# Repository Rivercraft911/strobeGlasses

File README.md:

# Strobe Glasses

Have you been seeing too much? Disappointed by the lack of stuttering in your reality? Introducing Strobe Glasses.

Open-source strobe glasses for experimenting with visual reaction-time training.

One LCD light valve slides into each side of the frame and switches between
light and dark at an adjustable rate. The goal is a small, USB-C rechargeable
control board that fits into a resin-printed glasses frame.

The MK1 PCB uses an ATtiny402, with USB-C charging and an output for each eye.

[KiCad project](strobeGlassesMK1/) · [Electronic parts](hardware-library/BOM.md) · [Glasses STEP](mechanical/strobe-glasses-mk1.step) · [Print and assemble](mechanical/TOP_LOAD.md) · [Firmware](firmware/strobe_glasses/)

Electrical decay after disabling the 5 V PSU output (90–10%: 477 ms).
Shorting the valve leads clears it much faster.

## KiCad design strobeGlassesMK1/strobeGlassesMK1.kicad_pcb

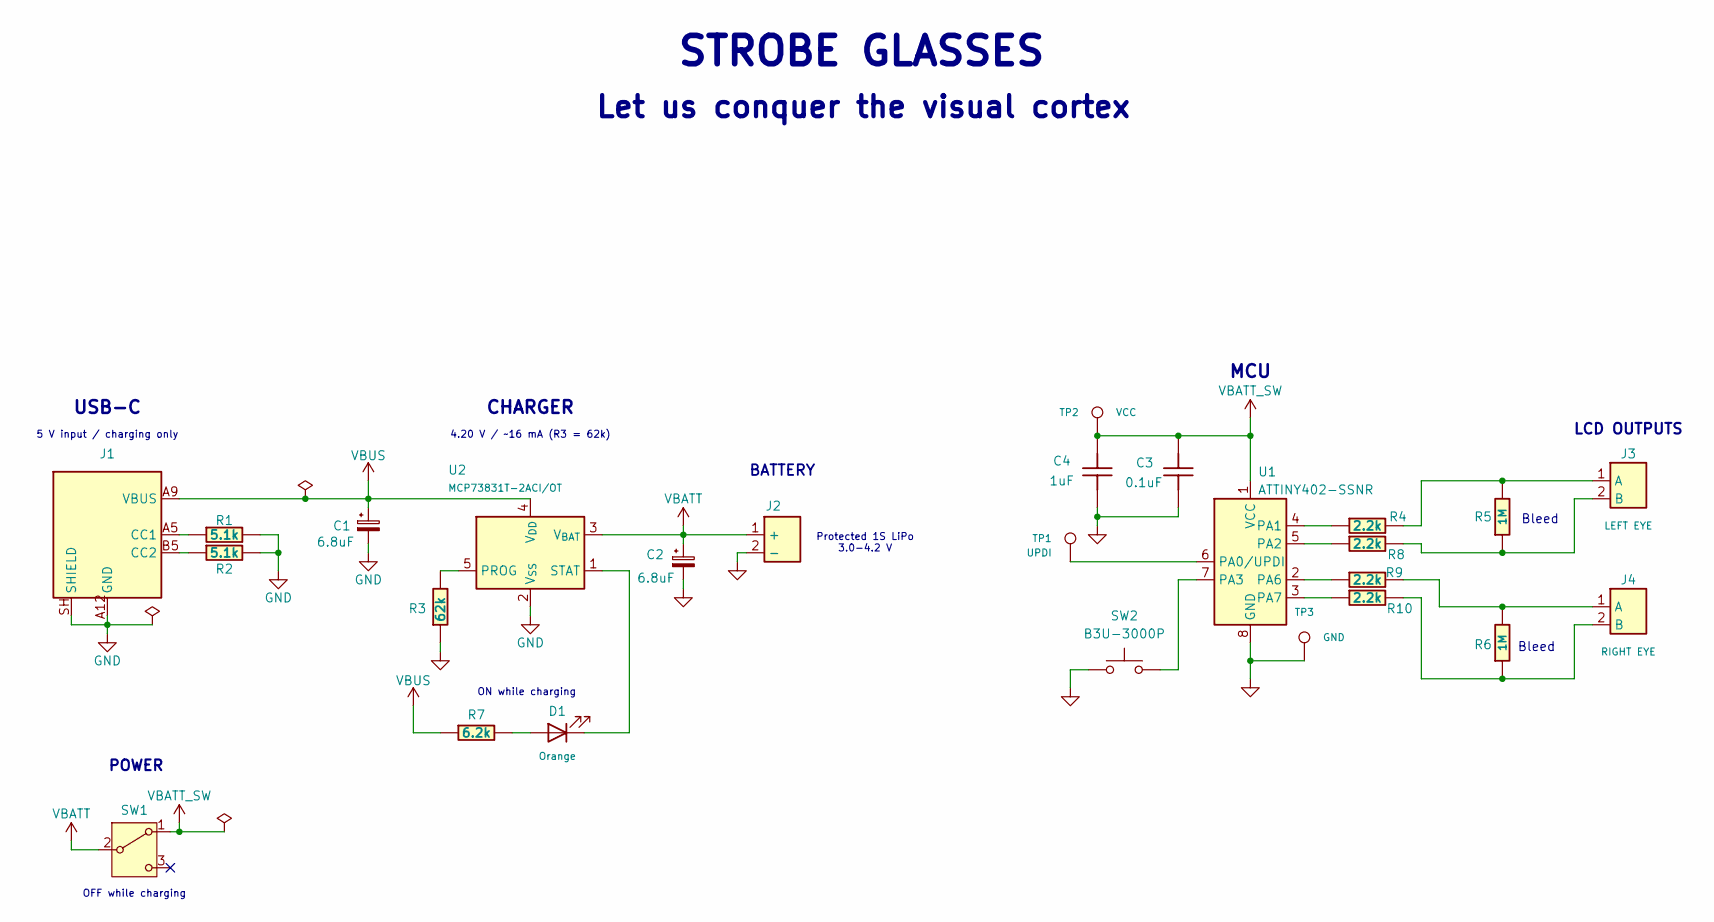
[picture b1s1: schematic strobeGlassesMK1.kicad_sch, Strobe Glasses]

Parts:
C1, C2: 6.8uF; T491A685K016AT; Rating 6.8 µF, 16 V, ±10%, polarized tantalum; MPN T491A685K016AT; DigiKey Part Number 399-10132-1-ND
C3: 0.1uF; C1608X7R1H104K080AA; Rating 100 nF, 50 V, X7R, ±10%, 0603; MPN C1608X7R1H104K080AA; DigiKey Part Number 445-1314-1-ND
C4: 1uF; CL10A105KP8NNNC; Rating 1 µF, 10 V, X5R, ±10%, 0603; MPN CL10A105KP8NNNC; DigiKey Part Number 1276-1182-1-ND
D1: Orange; LTST-C190KFKT; Rating Orange charge LED, 0603; MPN LTST-C190KFKT; DigiKey Part Number 160-1434-1-ND
J1: USB4125-GF-A; MPN USB4125-GF-A; DigiKey Part Number 2073-USB4125-GF-ACT-ND
J2: JST-SH 1mm; SM02B-SRSS-TB; MPN SM02B-SRSS-TB; DigiKey Part Number 455-SM02B-SRSS-TBCT-ND
J3: LEFT EYE; SM02B-SRSS-TB_LCD; MPN SM02B-SRSS-TB; DigiKey Part Number 455-SM02B-SRSS-TBCT-ND
J4: RIGHT EYE; SM02B-SRSS-TB_LCD; MPN SM02B-SRSS-TB; DigiKey Part Number 455-SM02B-SRSS-TBCT-ND
R1, R2: 5.1k; CRCW06035K10FKEA; Rating 5.1kohm ±1%, 0.125W, 0603; MPN CRCW06035K10FKEA; DigiKey Part Number 541-5.10KHCT-ND
R3: 62k; RC0603FR-0762KL; Rating 62.0 kΩ, ±1%, 0.1 W, 0603; MPN RC0603FR-0762KL; DigiKey Part Number 311-62.0KHRCT-ND
R4, R8, R9, R10: 2.2k; RC0603FR-072K2L; Rating 2.2 kΩ, ±1%, 0.1 W, 0603; MPN RC0603FR-072K2L; DigiKey Part Number 311-2.20KHRCT-ND
R5, R6: 1M; RC0603FR-071ML; Rating 1 MΩ, ±1%, 0.1 W, 0603; MPN RC0603FR-071ML; DigiKey Part Number 311-1.00MHRCT-ND
R7: 6.2k; RC0603FR-076K2L; Rating 6.2 kΩ, ±1%, 0.1 W, 0603; MPN RC0603FR-076K2L; DigiKey Part Number 311-6.20KHRCT-ND
SW1: SLW-662712-15A-SMT-TR; Rating SPDT, non-shorting, 6VDC, 300mA; body6.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; MPN SLW-662712-15A-SMT-TR; DigiKey Part Number 2223-SLW-662712-15A-SMT-TRCT-ND
SW2: B3U-3000P; Rating Side-actuated preset button; MPN B3U-3000P; DigiKey Part Number SW1022CT-ND
TP1: UPDI; TestPoint_Pad_D1.0mm
TP2: VCC; TestPoint_Pad_D1.0mm
TP3: GND; TestPoint_Pad_D1.0mm
U1: ATTINY402-SSNR; Rating 4 KB MCU, SOIC-8; MPN ATTINY402-SSNR; DigiKey Part Number ATTINY402-SSNRCT-ND
U2: MCP73831T-2ACI/OT; MCP73831T-2ACI_OT; Rating 4.20 V single-cell LiPo charger; MPN MCP73831T-2ACI/OT; DigiKey Part Number MCP73831T-2ACI/OTCT-ND

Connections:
GND: C1.2, C2.2, C3.2, C4.2, J1.A12 (GND), J1.B12 (GND), J1.SH (SHIELD), J2.2 (−), R1.2, R2.2, R3.1, SW2.1, TP3.1 (1_1), U1.8 (GND), U2.2 (V_{SS})
unnamed: D1.2 (A), R7.2
unnamed: D1.1 (K), U2.1 (STAT)
unnamed: J1.A5 (CC1), R1.1
unnamed: J1.B5 (CC2), R2.1
unnamed: J3.1 (A), R4.2, R5.2
unnamed: J3.2 (B), R5.1, R8.2
unnamed: J4.1 (A), R6.2, R9.2
unnamed: J4.2 (B), R6.1, R10.2
unnamed: TP1.1 (1_1), U1.6 (PA0/UPDI)
unnamed: R4.1, U1.4 (PA1)
unnamed: R8.1, U1.5 (PA2)
unnamed: SW2.2, U1.7 (PA3)
unnamed: R9.1, U1.2 (PA6)
unnamed: R10.1, U1.3 (PA7)
unnamed: R3.2, U2.5 (PROG)
VBATT: C2.1, J2.1 (+), SW1.2 (B), U2.3 (V_{BAT})
VBATT_SW: C3.1, C4.1, SW1.1 (A), TP2.1 (1_1), U1.1 (VCC)
VBUS: C1.1, J1.A9 (VBUS), J1.B9 (VBUS), R7.1, U2.4 (V_{DD})

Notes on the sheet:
Bleed
BATTERY
ON while charging
Protected 1S LiPo 3.0-4.2 V
USB-C
CHARGER
POWER
4.20 V / ~16 mA (R3 = 62k)
MCU
OFF while charging
LCD OUTPUTS
Let us conquer the visual cortex
STROBE GLASSES
5 V input / charging only

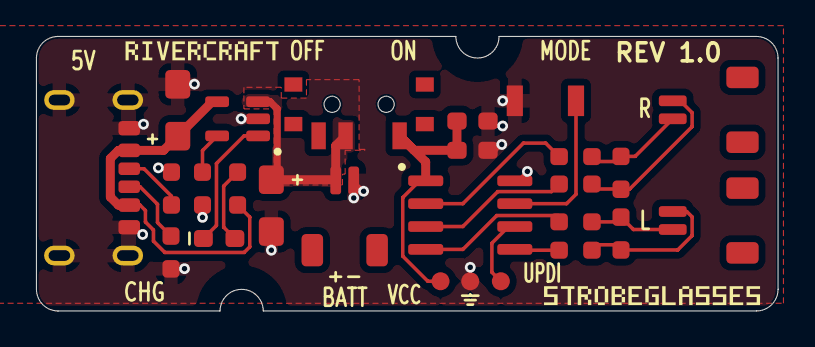
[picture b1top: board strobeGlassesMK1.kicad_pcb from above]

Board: 2 copper layers, 41.2 x 15.2 mm, 26 parts (0 on the bottom side), 19 nets.

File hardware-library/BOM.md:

# Order BOM

For **one fully populated PCB**: 23 purchased components, 15 order lines. TP1/TP2/TP3 are copper test pads and require no purchased parts. D1/R7 are included for the charge indicator.

- [DigiKey import: exact one-board quantities](digikey-bom.csv)
- [DigiKey import: one board with hand-assembly spares](digikey-bom-with-spares.csv)
- [DigiKey import: SH wiring parts](digikey-wiring.csv)
- [Independent board review](BOARD_REVIEW.md)

Use DigiKey “Upload a List” and map the part-number, quantity and reference columns. Select cut tape, not Digi-Reel. The spare list orders two each of ICs/switches/USB, five SH headers, four tantalum capacitors, ten of each small passive and five LEDs. Batteries, lenses and programmer are separate below.

| Qty | Refs | Part / value | Order MPN (DigiKey link) | DigiKey number |
| ---: | --- | --- | --- | --- |
| 1 | U1 | ATtiny402 MCU; SOIC-8 | [ATTINY402-SSNR](https://www.digikey.com/en/products/detail/microchip-technol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 | ATTINY402-SSNRCT-ND |
| 1 | U2 | 4.20 V LiPo charger; SOT-23-5 | [MCP73831T-2ACI/OT](https://www.digikey.com/en/products/detail/microchip-technol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 | MCP73831T-2ACI/OTCT-ND |
| 1 | J1 | 6-contact power-only USB-C; exact blank-suffix variant | [USB4125-GF-A](https://www.digikey.com/en/products/detail/gct/USB4125-GF-A/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 | 2073-USB4125-GF-ACT-ND |
| 3 | J2, J3, J4 | 2-pin JST-SH 1 mm right-angle headers | [SM02B-SRSS-TB](https://www.digikey.com/en/products/detail/jst-sales-america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 | 455-SM02B-SRSS-TBCT-ND |
| 1 | SW1 | Hard power slide switch | [SLW-662712-15A-SMT-TR](https://www.digikey.com/en/products/detail/same-sky-formerly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 | 2223-SLW-662712-15A-SMT-TRCT-ND |
| 1 | SW2 | Side-actuated preset button | [B3U-3000P](https://www.digikey.com/en/products/detail/omron-electronics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 | SW1022CT-ND |
| 2 | C1, C2 | 6.8 uF 16 V tantalum; KEMET A-case; polarized | [T491A685K016AT](https://www.digikey.com/en/products/detail/kemet/T491A685K01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 | 399-10132-1-ND |
| 1 | C3 | 100 nF 50 V X7R; 0603 | [C1608X7R1H104K080AA](https://www.digikey.com/en/products/detail/tdk/C1608X7R1H104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 | 445-1314-1-ND |
| 1 | C4 | 1 uF 10 V X5R; 0603 | [CL10A105KP8NNNC](https://www.digikey.com/en/products/detail/samsung-electro-m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 | 1276-1182-1-ND |
| 2 | R1, R2 | 5.1 kohm 1% 0.125 W; 0603; USB CC pull-downs | [CRCW06035K10FKEA](https://www.digikey.com/en/products/detail/vishay-dale/CRCW0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 | 541-5.10KHCT-ND |
| 1 | R3 | 62 kohm 1% 0.1 W; 0603; ~16.1 mA charge setting | [RC0603FR-0762KL](https://www.digikey.com/en/products/detail/yageo/RC0603FR-07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 | 311-62.0KHRCT-ND |
| 4 | R4, R8, R9, R10 | 2.2 kohm 1% 0.1 W; 0603; four LCD series resistors | [RC0603FR-072K2L](https://www.digikey.com/en/products/detail/yageo/RC0603FR-07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 | 311-2.20KHRCT-ND |
| 2 | R5, R6 | 1 Mohm 1% 0.1 W; 0603; eye bleeders | [RC0603FR-071ML](https://www.digikey.com/en/products/detail/yageo/RC0603FR-07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 | 311-1.00MHRCT-ND |
| 1 | R7 | 6.2 kohm 1% 0.125 W; 0603; charge LED resistor | [CRCW06036K20FKEA](https://www.digikey.com/en/products/detail/vishay-dale/CRCW0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 | 541-6.20KHCT-ND |
| 1 | D1 | Orange LED; 0603; pad 1 cathode | [LTST-C190KFKT](https://www.digikey.com/en/products/detail/liteon/LTST-C190K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 | 160-1434-1-ND |

**R7 substitution:** the selected Yageo RC0603FR-076K2L showed zero stock. The order files use Vishay CRCW06036K20FKEA, an equivalent 6.2 kohm, 1%, 0603 part with a higher 0.125 W rating. CAD selection is unchanged. Omit both R7 and D1 if you do not want a charge indicator.

All order lines above showed stock during the 2026-11-08 US DigiKey check. The exact one-board PCB parts total is about **$7.41** at the displayed one-piece prices, before shipping/tax/tariffs. Quantity discounts may lower it. Stock and checkout prices can change.

## Wiring and offboard items

| Qty | Item | MPN / DigiKey link | DigiKey number | When needed |
| ---: | --- | --- | --- | --- |
| 3 | JST-SH 2-pin cable housings | [SHR-02V-S-B](https://www.digikey.com/en/products/detail/jst-sales-america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 | 455-1377-ND | One per cable; two for eyes, plus battery adapter if reusing the PH pack. One is spare if buying the factory-SH battery. |
| 6 | Black 28 AWG precrimped wires, 152.4 mm, socket at both ends | [ASSHSSH28K152](https://www.digikey.com/en/products/detail/jst-sales-america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 | 455-3076-ND | Lets you keep long leads for three pigtails. Cut near one end or split into shorter leads; three assemblies suffice if halved. Mark polarity clearly. |
| 1 optional | PH male pigtail for on-hand Adafruit battery | [Adafruit 3814](https://www.digikey.com/en/products/detail/adafruit-industri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 | 1528-2617-ND | Splice to an SH pigtail to adapt the existing PH battery without changing its factory lead. Not needed with the SparkFun 40 mAh pack. |
| 1 if needed | UPDI programmer, cable included | [Adafruit 5879](https://www.digikey.com/en/products/detail/adafruit-industri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 | 1528-5879-ND | If you do not already own a suitable UPDI programmer. Temporarily wire to TP1/TP2/TP3. |
| 4 total | Small LCD light valves | [Adafruit 3627](https://www.digikey.com/en/products/detail/adafruit-industri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 | 1528-2516-ND | Two stacked, electrically parallel per eye. Buy only any shortfall from the valves already on hand. |

## Battery choice

Use the protected Adafruit/PKCELL 105 mAh pack already on hand for first bring-up, or try **[SparkFun 25270, 40 mAh](https://www.digikey.com/en/products/detail/sparkfun-electron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 / **1568-25270-ND** for the smaller build. The latter showed 267 in stock at $7.39. The finished protected pack is at most 22 × 11.5 × 3.5 mm, and its datasheet specifies SHR-02V-S-B with pin 1 red(+)/pin 2 black(-), matching J2 directly.

The 40 mAh pack specifies 8 mA standard charge and 20 mA maximum. This board is ~16.1 mA nominal, so it is below the maximum, with margin in the checked datasheet corners. Its taper endpoint differs from the charger; measure usable capacity/current on the final board before promising runtime. Keep R3 = 62 kΩ: arbitrarily increasing RPROG past 67 kΩ is outside the MCP73831 specified range and approaches shutdown detection.

Battery size can shrink now without changing the PCB, because only its connector is modeled. Keep enclosure clearance for the entire protected pack, its lead and the connector. Confirm actual cable polarity before connection. Measure the final ATtiny board current before choosing the final capacity.

[40 mAh pack specification](https://cdn.sparkfun.com/assets/4/f/c/6/3/SPE-DTP301120SH-3.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 · [SparkFun product](https://www.sparkfun.com/polymer-lithium-ion-battery-40mah-j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

## First-board conditions

- Charge with SW1 OFF; the charger has no load sharing. Use a protected 1S LiPo (3.7 V nominal, 4.2 V full).
- Program a conservative 5 MHz or slower ATtiny application, with balanced positive/negative LCD drive, clear-on-reset, button pull-up/debounce and brownout/low-battery handling.
- For UPDI Friend bring-up: SW1 OFF, Friend at 3.3 V, PWR to TP2, GND to TP3 and UPDI to TP1. Avoid tying its power output to a battery-driven rail.
- Check actual charging current, UPDI operation, lens voltage/contrast and board battery current on the assembled prototype. Mechanical fit follows; no PCB change is currently required by the review.

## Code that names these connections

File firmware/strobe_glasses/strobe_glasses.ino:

#include <Arduino.h>
#include <avr/eeprom.h>
#include <avr/interrupt.h>
#include <avr/sleep.h>
#include <avr/wdt.h>
#include <util/atomic.h>

#if !defined(__AVR_ATtiny402__) || F_CPU != 5000000UL
#error "Select ATtiny402 and 5 MHz internal."
#endif
#if !defined(MILLIS_USE_TIMERA0) && !defined(MILLIS_USE_TIMERNONE)
#error "Use the default ATtiny402 millis timer (TCA0) or disable millis."
#endif

// MK1: PA0 stays dedicated to UPDI. The charge LED has no MCU connection.
constexpr uint8_t LensPins = PIN1_bm | PIN2_bm | PIN6_bm | PIN7_bm;
constexpr uint8_t ButtonPin = PIN3_bm;

constexpr uint8_t Rates[] = {2, 4, 5, 6, 8, 10, 15, 20};
constexpr uint8_t DutySteps = 7;  // 20% through 80%, in 10-point steps
constexpr uint8_t Custom = 3;
constexpr uint16_t HoldMs = 800;
constexpr uint8_t DebounceMs = 25;
constexpr uint16_t DoubleTapMs = 300;
constexpr uint16_t EditPauseMs = 600;

struct Tuning {
  uint8_t rateIndex;
  uint8_t dutyIndex;
};

constexpr Tuning Presets[] = {
  {3, 2},  // Light: 6 fps, 40% dark
  {2, 3},  // Balanced: 5 fps, 50% dark
  {1, 4},  // Heavy: 4 fps, 60% dark
};

enum class Mode : uint8_t { Clear, Playing, AdjustRate, AdjustDuty };
// Two GPIO bits per eye: 00 shorts the electrodes, 01 and 10 drive the LCD.
enum class Phase : uint8_t { Clear = 0, Positive = 1, Negative = 2 };

struct FrameTiming {
  uint16_t clearMs;
  uint8_t pairs;
  uint8_t halfMs;
  uint8_t longerPairs;
  uint8_t rightDelayMs;
};

// Byte 0 keeps the original preset/rate/duty encoding. An erased byte 1
// selects together mode on both a fresh chip and an existing MK1.
uint8_t EEMEM savedSettings[2] = {0xff, 0xff};
bool alternating = false;
uint8_t selectedPreset = 0;
Tuning custom = Presets[1];
Tuning draft;
Mode mode = Mode::Clear;
bool previewPaused = false;
uint16_t pauseStartedMs = 0;

bool rawPressed = false;
bool pressed = false;
bool holdHandled = false;
uint16_t buttonChangedMs = 0;
uint16_t pressStartedMs = 0;
bool tapPending = false;
uint16_t tapReleasedMs = 0;

volatile uint16_t ticksMs = 0;
volatile FrameTiming requested = {};  // zero pairs requests clear
volatile bool timingChanged = false;
FrameTiming active;

struct Eye {
  Phase phase;
  uint16_t remainingMs;
  uint8_t pairsLeft;
  uint8_t longerPairs;
  uint8_t pairHalfMs;
};
Eye leftEye = {}, rightEye = {};

void tickEye(Eye &eye, bool stopping) {
  if (stopping && eye.phase == Phase::Clear) return;
  if (--eye.remainingMs) return;
  switch (eye.phase) {
    case Phase::Clear:
      eye.pairsLeft = active.pairs;
      eye.longerPairs = active.longerPairs;
      break;
    case Phase::Positive:
      eye.phase = Phase::Negative;
      eye.remainingMs = eye.pairHalfMs;
      return;
    case Phase::Negative:
      if (stopping || --eye.pairsLeft == 0) {
        eye.phase = Phase::Clear;
        eye.remainingMs = active.clearMs;
        return;
      }
      break;
  }
  eye.pairHalfMs = active.halfMs;
  if (eye.longerPairs) {
    ++eye.pairHalfMs;
    --eye.longerPairs;
  }
  eye.phase = Phase::Positive;
  eye.remainingMs = eye.pairHalfMs;
}

ISR(TCB0_INT_vect) {
  TCB0.INTFLAGS = TCB_CAPT_bm;
  ++ticksMs;
  // Finish each eye's current AC pair before restarting the two envelopes.
  if (timingChanged && leftEye.phase == Phase::Clear && rightEye.phase == Phase::Clear) {
    active = {requested.clearMs, requested.pairs, requested.halfMs,
              requested.longerPairs, requested.rightDelayMs};
    leftEye.remainingMs = 1;
    rightEye.remainingMs = 1 + active.rightDelayMs;
    timingChanged = false;
  }
  if (!active.pairs) return;
  tickEye(leftEye, timingChanged);
  tickEye(rightEye, timingChanged);
  // J3 uses PA1/PA2 and J4 uses PA6/PA7. Update all electrodes together.
  VPORTA.OUT = (VPORTA.OUT & ~LensPins) | (uint8_t(leftEye.phase) << 1)
               | (uint8_t(rightEye.phase) << 6);
}

Tuning selectedTuning() {
  return selectedPreset == Custom ? custom : Presets[selectedPreset];
}

void updateTiming() {
  FrameTiming timing = {};
  if (mode != Mode::Clear && !previewPaused) {
    const Tuning tuning = mode == Mode::Playing ? selectedTuning() : draft;
    const uint8_t fps = Rates[tuning.rateIndex];
    const uint8_t duty = 20 + 10 * tuning.dutyIndex;
    const uint16_t frameMs = (1000 + fps / 2) / fps;
    // Round to an even number of milliseconds and divide the dark window
    // into complete pairs near 100 Hz. Each pair has equal +/- durations.
    const uint16_t darkHalfMs = (frameMs * duty + 100) / 200;
    timing.clearMs = frameMs - 2 * darkHalfMs;
    timing.pairs = (darkHalfMs + 2) / 5;
    timing.halfMs = darkHalfMs / timing.pairs;
    timing.longerPairs = darkHalfMs % timing.pairs;
    timing.rightDelayMs = alternating ? frameMs / 2 : 0;
  }
  ATOMIC_BLOCK(ATOMIC_RESTORESTATE) {
    requested.clearMs = timing.clearMs;
    requested.pairs = timing.pairs;
    requested.halfMs = timing.halfMs;
    requested.longerPairs = timing.longerPairs;
    requested.rightDelayMs = timing.rightDelayMs;
    timingChanged = true;
  }
}

void loadSettings() {
  alternating = eeprom_read_byte(&savedSettings[1]) == 1;
  const uint8_t settings = eeprom_read_byte(&savedSettings[0]);
  const uint8_t dutyIndex = settings & 0x07;
  if (dutyIndex >= DutySteps) return;  // Includes erased EEPROM (0xff).
  selectedPreset = settings >> 6;
  custom = {uint8_t((settings >> 3) & 0x07), dutyIndex};
}

void saveSettings() {
  eeprom_update_byte(&savedSettings[0],
                     (selectedPreset << 6) | (custom.rateIndex << 3) | custom.dutyIndex);
}

void tap() {
  switch (mode) {
    case Mode::Clear:
      mode = Mode::Playing;
      break;
    case Mode::Playing:
      selectedPreset = (selectedPreset + 1) % (Custom + 1);
      saveSettings();
      break;
    case Mode::AdjustRate:
      draft.rateIndex = (draft.rateIndex + 1) % sizeof(Rates);
      break;
    case Mode::AdjustDuty:
      draft.dutyIndex = (draft.dutyIndex + 1) % DutySteps;
      break;
  }
  updateTiming();
}

void hold(uint16_t now) {
  switch (mode) {
    case Mode::Playing:
      mode = Mode::Clear;
      break;
    case Mode::Clear:
      draft = selectedTuning();
      mode = Mode::AdjustRate;
      break;
    case Mode::AdjustRate:
      mode = Mode::AdjustDuty;
      previewPaused = true;
      pauseStartedMs = now;
      break;
    case Mode::AdjustDuty:
      custom = draft;
      selectedPreset = Custom;
      mode = Mode::Playing;
      previewPaused = true;
      pauseStartedMs = now;
      saveSettings();
      break;
  }
  updateTiming();
}

void readButton(uint16_t now) {
  if (tapPending && !pressed && !rawPressed && uint16_t(now - tapReleasedMs) >= DoubleTapMs) {
    tapPending = false;
    tap();
  }
  const bool down = !(VPORTA.IN & ButtonPin);
  if (down != rawPressed) {
    rawPressed = down;
    buttonChangedMs = now;
  }
  if (rawPressed != pressed && uint16_t(now - buttonChangedMs) >= DebounceMs) {
    pressed = rawPressed;
    if (pressed) {
      pressStartedMs = now;
      holdHandled = false;
    } else if (!holdHandled) {
      if (mode != Mode::Playing) {
        tap();
      } else if (tapPending) {
        tapPending = false;
        alternating = !alternating;
        updateTiming();
        eeprom_update_byte(&savedSettings[1], alternating);
      } else {
        tapPending = true;
        tapReleasedMs = now;
      }
    }
  }
  if (pressed && rawPressed && !holdHandled && uint16_t(now - pressStartedMs) >= HoldMs) {
    holdHandled = true;
    tapPending = false;
    hold(now);
  }
}

void setup() {
  PORTA.OUTCLR = LensPins;
  PORTA.DIRSET = LensPins;
  PORTA.PIN3CTRL = PORT_PULLUPEN_bm;
  rawPressed = pressed = holdHandled = !(VPORTA.IN & ButtonPin);
  loadSettings();

  // The sketch uses TCB0 for all timing. Stop the core's default TCA0 tick.
  TCA0.SINGLE.CTRLA = 0;
  TCA0.SPLIT.INTCTRL = 0;
  TCB0.CTRLA = 0;
  TCB0.CTRLB = TCB_CNTMODE_INT_gc;
  TCB0.CCMP = F_CPU / 2 / 1000 - 1;
  TCB0.CNT = 0;
  TCB0.INTFLAGS = TCB_CAPT_bm;
  TCB0.INTCTRL = TCB_CAPT_bm;
  TCB0.CTRLA = TCB_CLKSEL_CLKDIV2_gc | TCB_ENABLE_bm;
  set_sleep_mode(SLEEP_MODE_IDLE);
  wdt_reset();
  _PROTECTED_WRITE(WDT.CTRLA, WDT_PERIOD_1KCLK_gc);
}

void loop() {
  static uint16_t lastTick = 0;
  uint16_t now;
  ATOMIC_BLOCK(ATOMIC_RESTORESTATE) {
    now = ticksMs;
  }
  if (now != lastTick) {
    lastTick = now;
    wdt_reset();
    readButton(now);
    if (previewPaused && uint16_t(now - pauseStartedMs) >= EditPauseMs) {
      previewPaused = false;
      updateTiming();
    }
  }
  sleep_mode();
}

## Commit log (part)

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2025-09-28 Lots of general fixes and changes
